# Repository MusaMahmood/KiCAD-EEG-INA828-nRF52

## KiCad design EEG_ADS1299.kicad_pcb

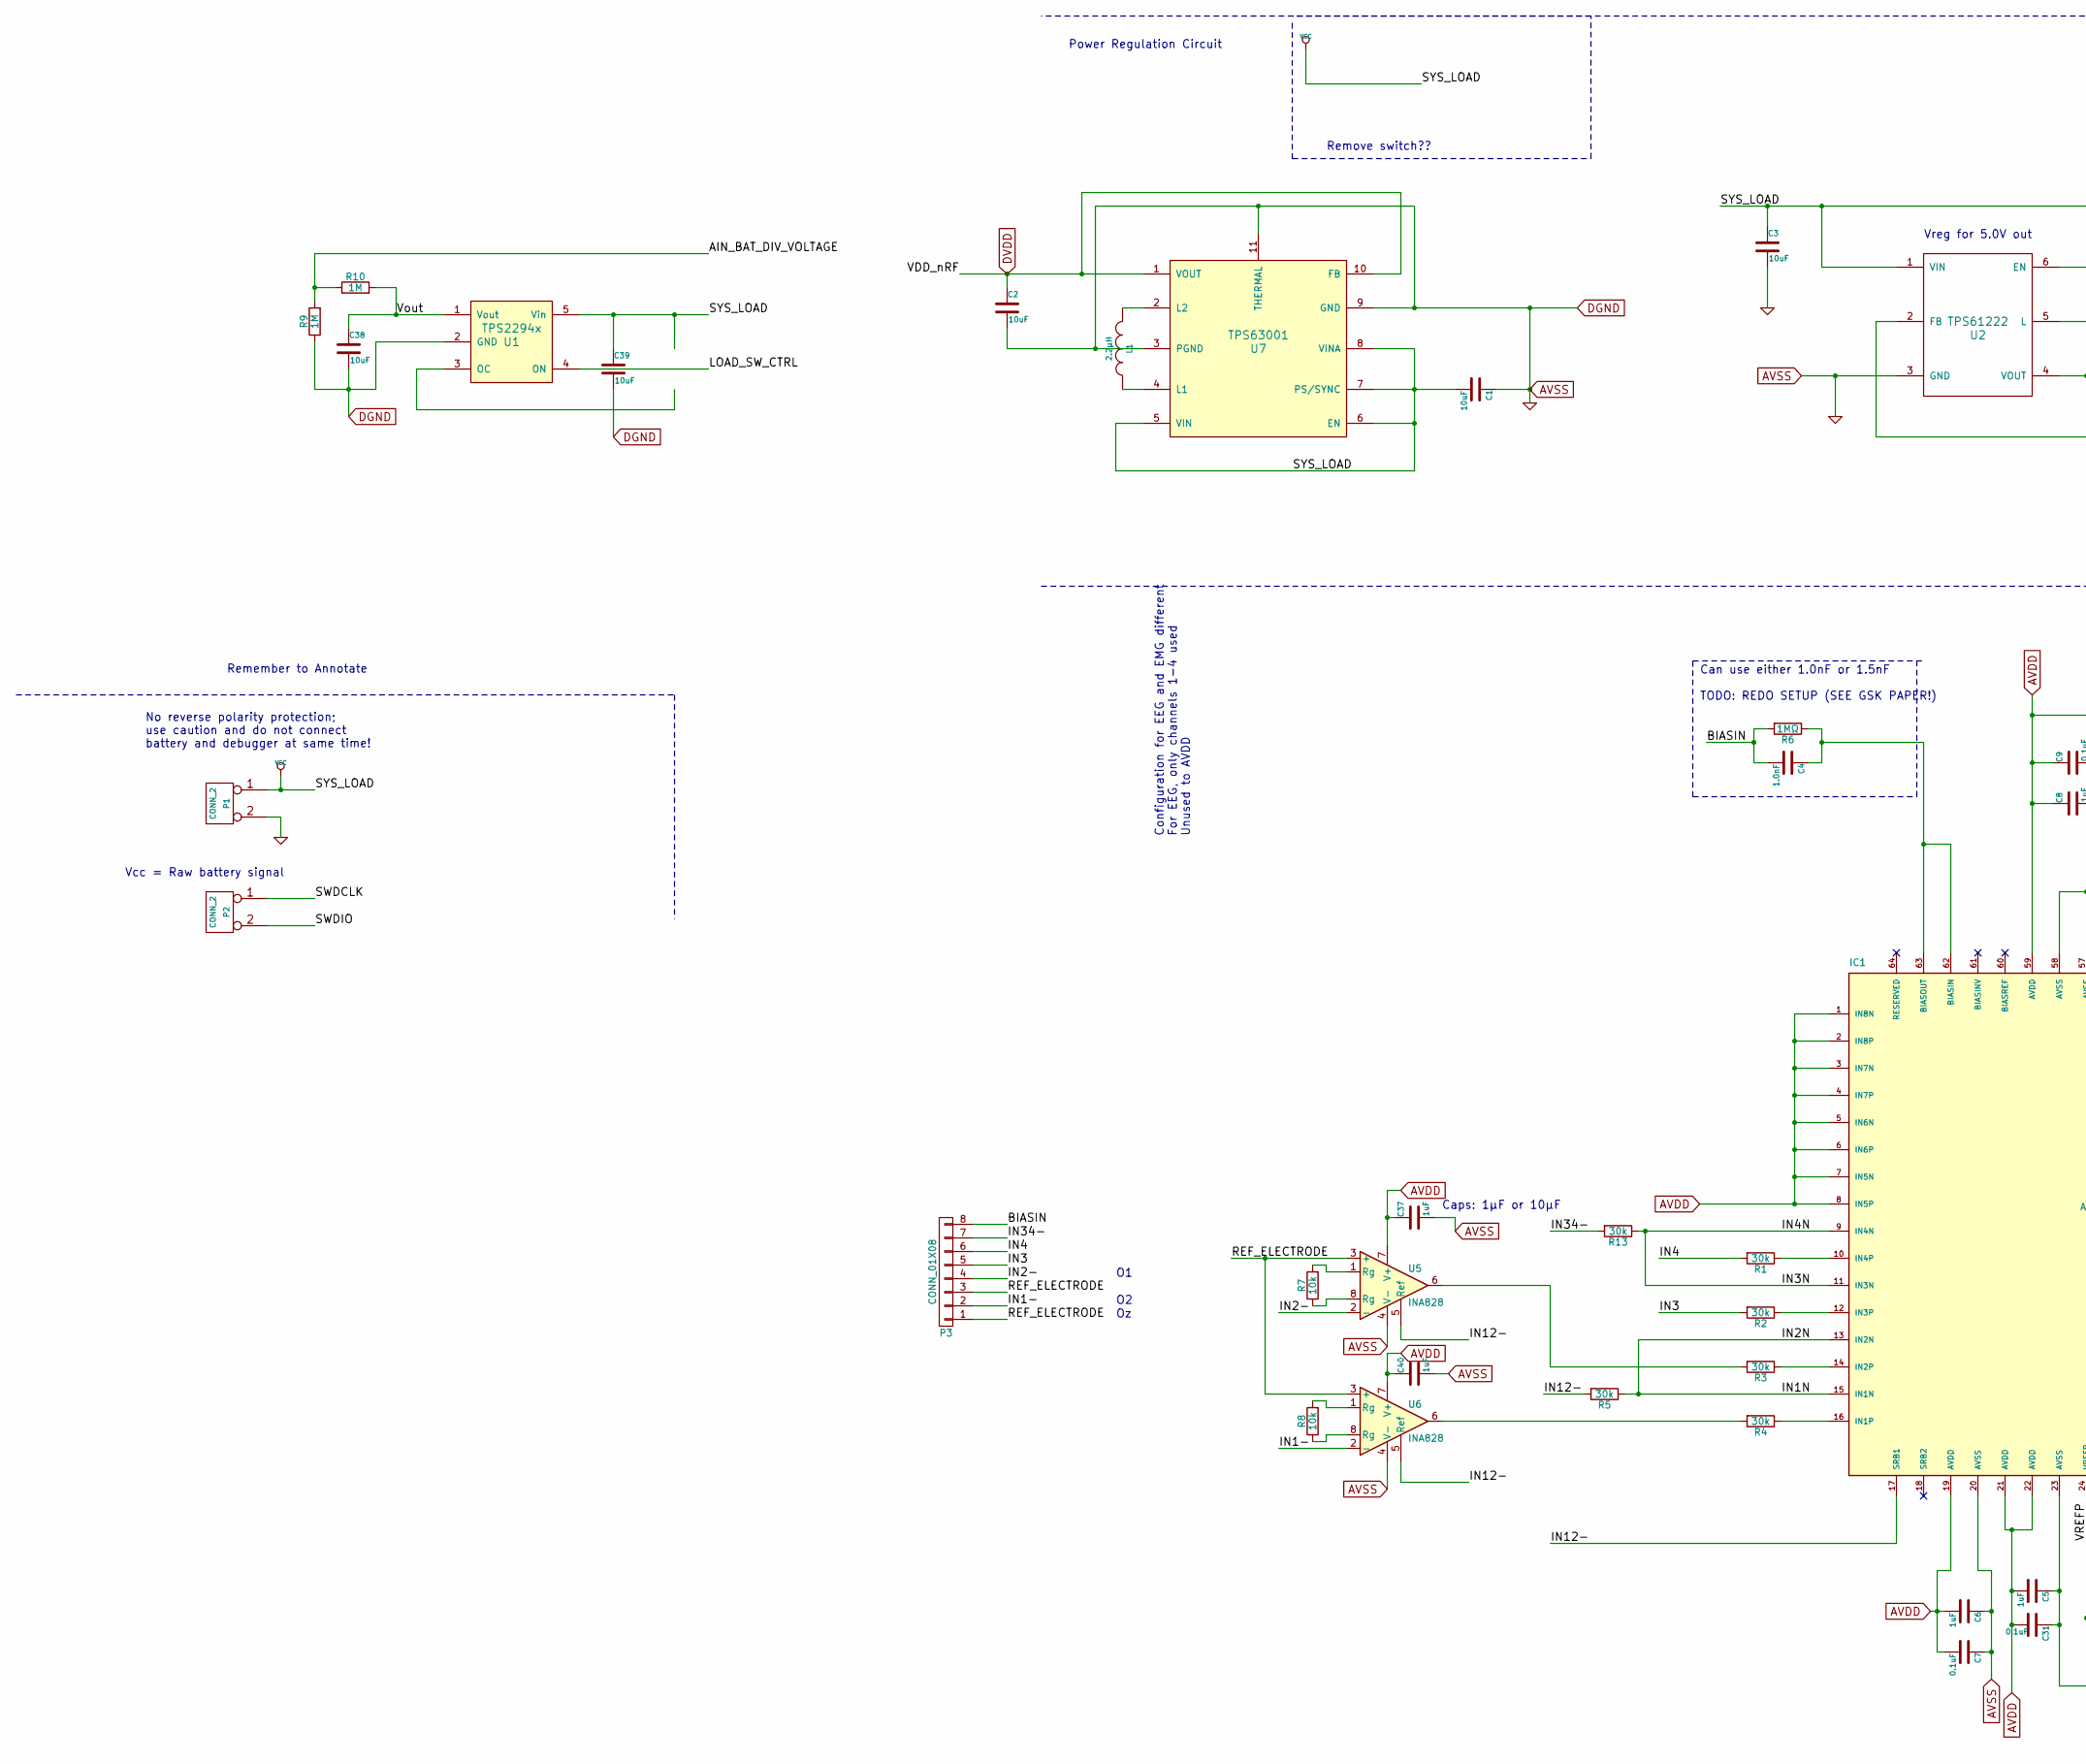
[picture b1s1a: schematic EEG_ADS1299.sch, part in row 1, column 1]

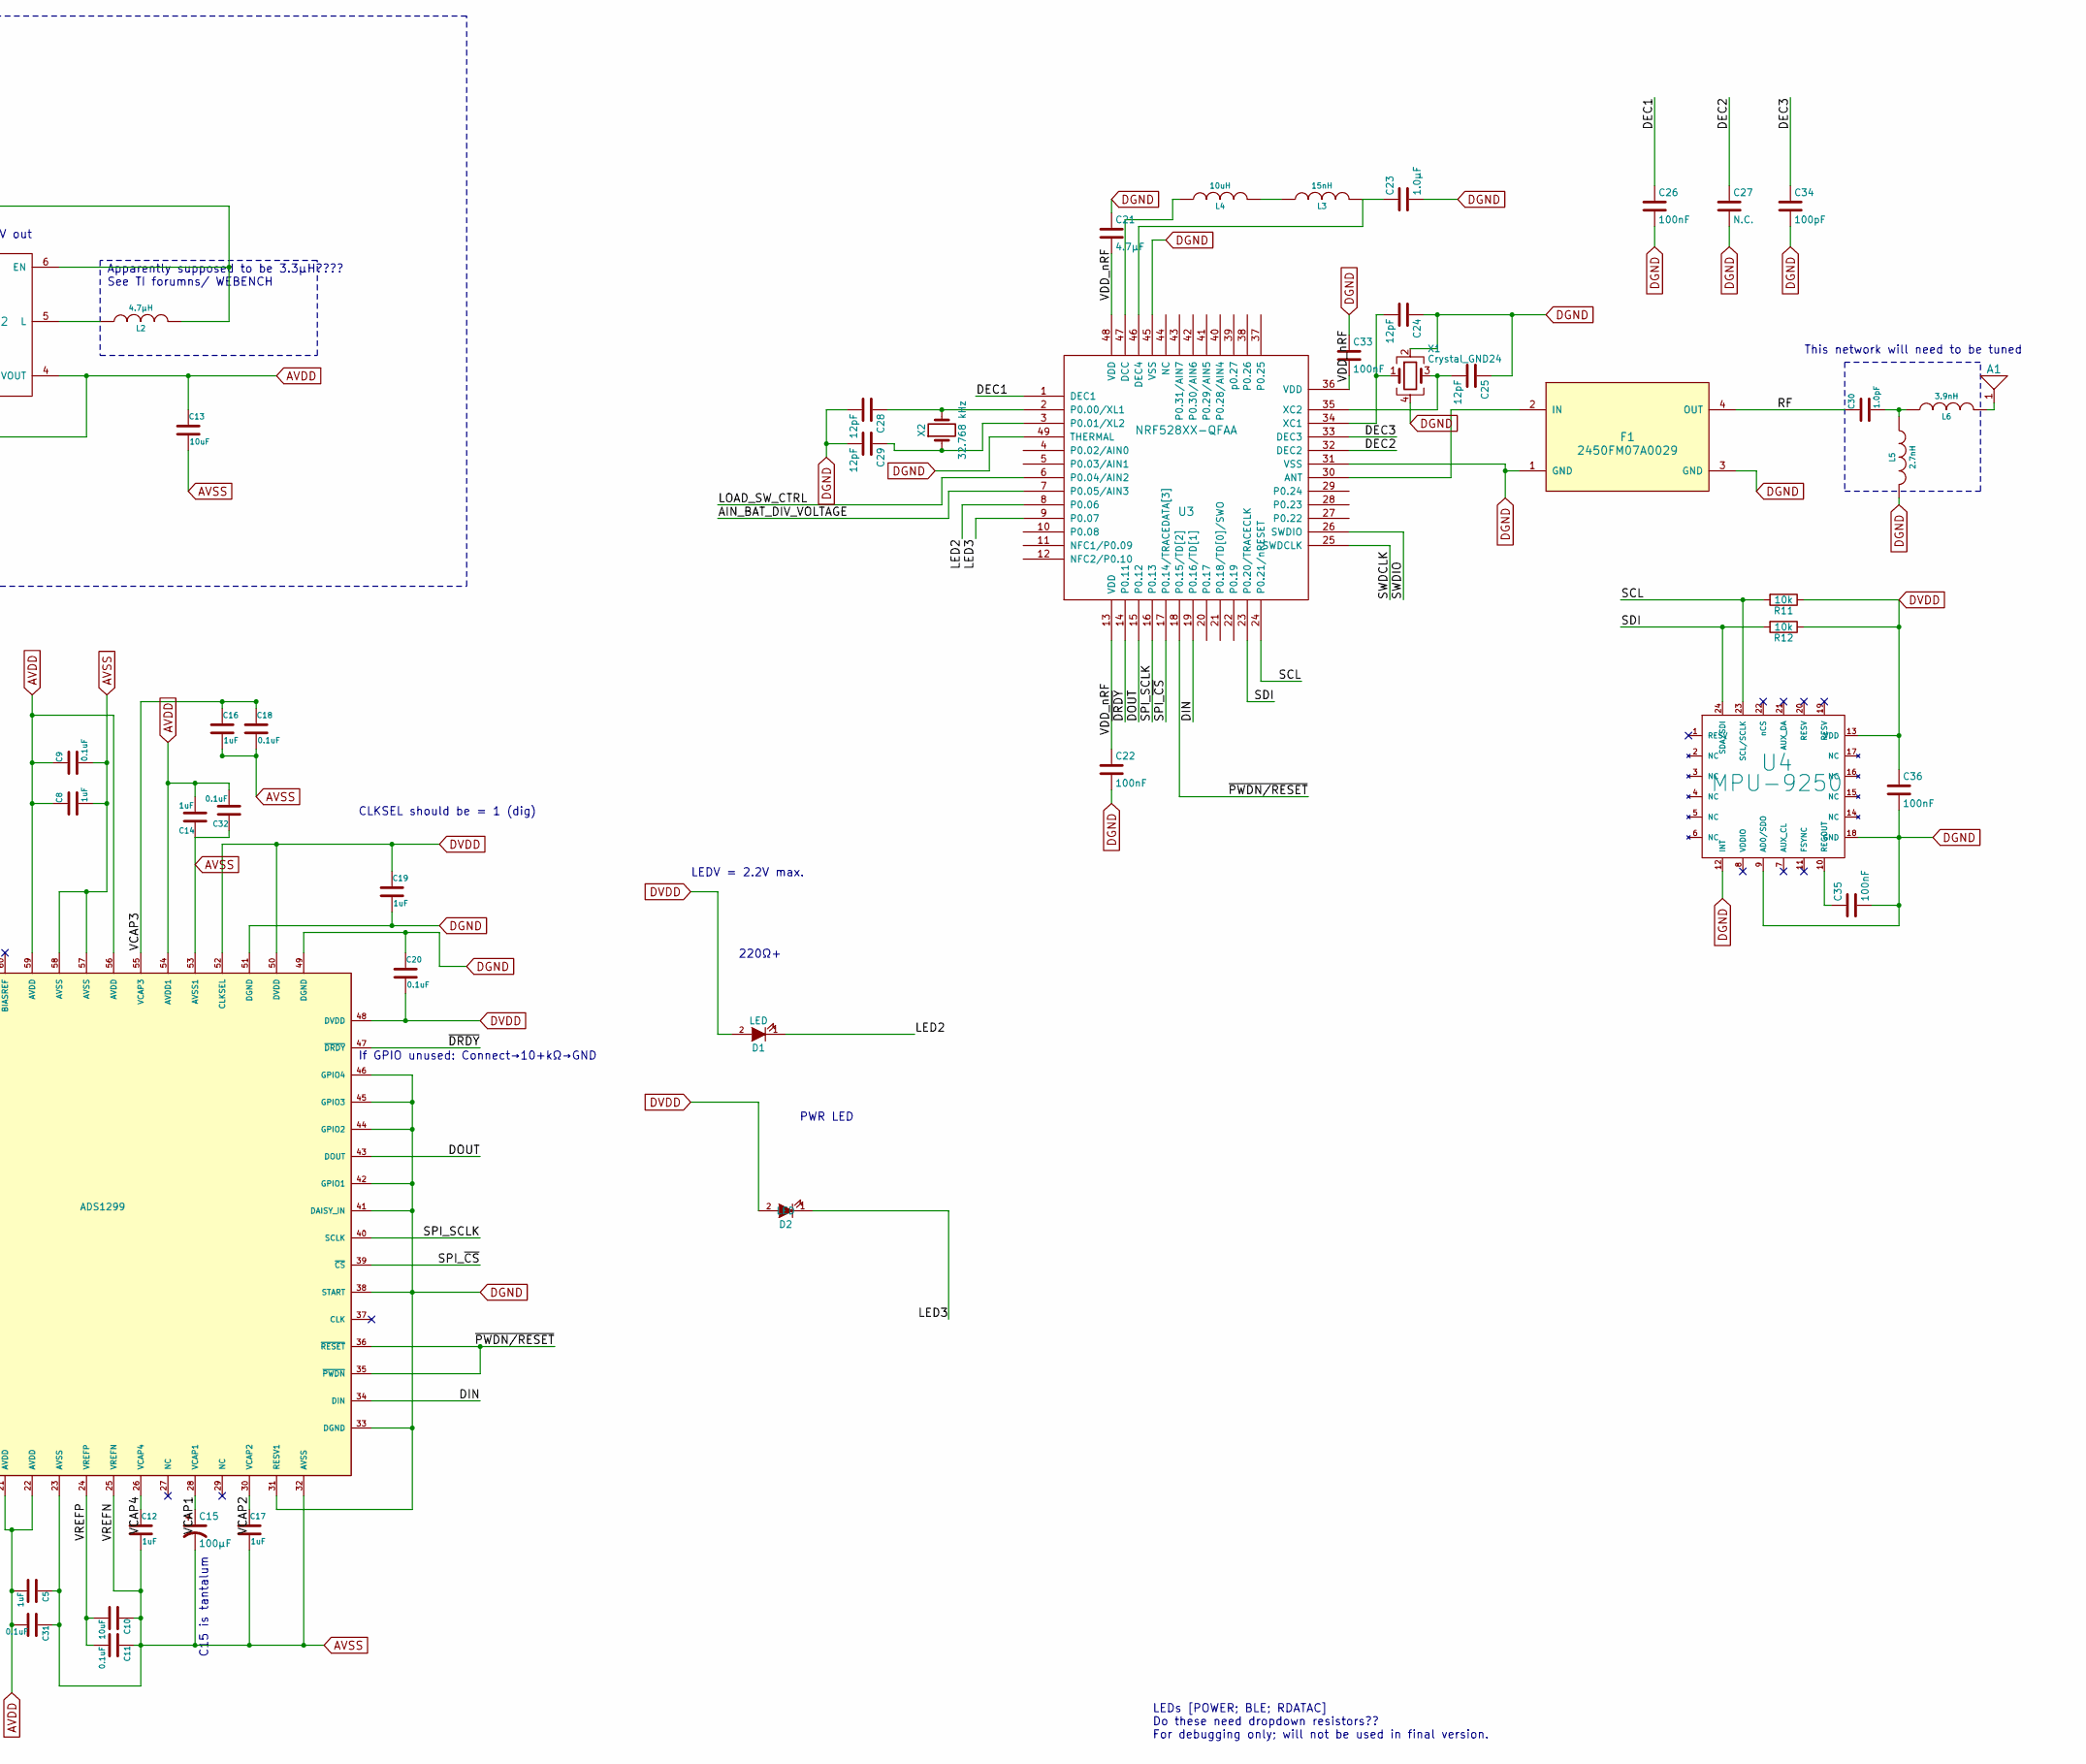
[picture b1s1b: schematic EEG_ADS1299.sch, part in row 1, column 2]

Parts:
A1: CHIP-ANT
C1, C2, C3, C13, C38, C39: 10uF; C_0402
C4: 1.0nF; C_0402
C5, C6, C8, C12, C14, C16, C17, C19, C37, C40: 1uF; C_0402
C7, C9, C11, C18, C20, C31, C32: 0.1uF; C_0402
C10: 10uF; C_0603
C15: 100µF; C_0603
C21: 4.7µF; C_0402
C22: 100nF; C_0603
C23: 1.0µF; C_0603
C24, C25, C28, C29: 12pF; C_0402
C26, C33, C35, C36: 100nF; C_0402
C27: N.C.
C30: 1.0pF; C_0402
C34: 100pF; C_0402
D1, D2: LED; LED_0603
F1: 2450FM07A0029
IC1: ADS1299; TQFP-64_10x10mm_Pitch0.5mm
L1: 2.2µH; L_0603
L2: 4.7µH; L_0603
L3: 15nH; L_0402
L4: 10uH; L_0603
L5: 2.7nH; L_0402
L6: 3.9nH; L_0402
P1, P2: CONN_2; Pin_Header_Straight_1x02_Pitch2.54mm
P3: CONN_01X08
R1, R2, R3, R4, R5, R13: 30k; R_0402
R6: 1MΩ; R_0402
R7, R8, R11, R12: 10k; R_0402
R9, R10: 1M; R_0402
U1: TPS2294x; SOT-353_SC-70-5
U2: TPS61222; SOT-363_SC-70-6
U3: NRF528XX-QFAA; UQFN-48-1EP_6x6mm_Pitch0.4mm
U4: MPU-9250; QFN-24_3x3mm_Pitch0.4mm
U5, U6: INA828; SOIC_8_4.9mm_x_3.91
U7: TPS63001; DFN-10-1EP_3x3mm_Pitch0.5mm
X1: Crystal_GND24; Crystal_SMD_2016-4pin_2.0x1.6mm
X2: 32.768 kHz; Crystal_SMD_2012-2pin_2.0x1.2mm

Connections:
/AIN_BAT_DIV_VOLTAGE: R9.2, R10.1, U3.7 (P0.05/AIN3)
/BIASIN: C4.2, P3.8, R6.2
/DEC1: C26.1, U3.1 (DEC1)
/DEC2: C27.1, U3.32 (DEC2)
/DEC3: C34.1, U3.33 (DEC3)
/DIN: IC1.34 (DIN), U3.19 (P0.16/TD[1])
/DOUT: IC1.43 (DOUT), U3.15 (P0.12)
/IN1-: P3.2, U6.2 (-)
/IN1N: IC1.13 (IN2N), IC1.15 (IN1N), R5.1
/IN2-: P3.4, U5.2 (-)
/IN3: P3.5, R2.2
/IN3N: IC1.9 (IN4N), IC1.11 (IN3N), R13.1
/IN4: P3.6, R1.2
/IN12-: IC1.17 (SRB1), R5.2, U5.5 (Ref), U6.5 (Ref)
/IN34-: P3.7, R13.2
/LED2: D1.1 (K), U3.8 (P0.06)
/LED3: D2.1 (K), U3.9 (P0.07)
/LOAD_SW_CTRL: U1.4 (ON), U3.6 (P0.04/AIN2)
/REF_ELECTRODE: P3.1, P3.3, U5.3 (+), U6.3 (+)
/RF: C30.1, F1.4 (OUT)
/SCL: R11.2, U3.24 (P0.21/nRESET), U4.23 (SCL/SCLK)
/SDI: R12.2, U3.23 (P0.20/TRACECLK), U4.24 (SDA/SDI)
/SPI_SCLK: IC1.40 (SCLK), U3.16 (P0.13)
/SPI_~CS: IC1.39 (~CS), U3.17 (P0.14/TRACEDATA[3])
/SWDCLK: P2.1, U3.25 (SWDCLK)
/SWDIO: P2.2 (PM), U3.26 (SWDIO)
/VCAP1: C15.1, IC1.28 (VCAP1)
/VCAP2: C17.1, IC1.30 (VCAP2)
/VCAP3: C16.1, C18.1, IC1.55 (VCAP3)
/VCAP4: C12.1, IC1.26 (VCAP4)
/VREFP: C10.2, C11.2, IC1.24 (VREFP)
/Vout: C38.1, R10.2, U1.1 (Vout)
/~DRDY: IC1.47 (~DRDY), U3.14 (P0.11)
/~PWDN/RESET: IC1.35 (~PWDN), IC1.36 (~RESET), U3.18 (P0.15/TD[2])
AVDD: C5.2, C6.2, C7.2, C8.1, C9.1, C13.1, C14.2, C31.2, C32.2, C37.1, C40.1, IC1.1 (IN8N), IC1.2 (IN8P), IC1.3 (IN7N), IC1.4 (IN7P), IC1.5 (IN6N), IC1.6 (IN6P), IC1.7 (IN5N), IC1.8 (IN5P), IC1.19 (AVDD), IC1.21 (AVDD), IC1.22 (AVDD), IC1.54 (AVDD1), IC1.56 (AVDD), IC1.59 (AVDD), U2.2 (FB), U2.4 (VOUT), U5.7 (V+), U6.7 (V+)
AVSS: C1.1, C2.2, C3.2, C5.1, C6.1, C7.1, C8.2, C9.2, C10.1, C11.1, C12.2, C13.2, C14.1, C15.2, C16.2, C17.2, C18.2, C19.2, C20.1, C21.1, C22.2, C23.2, C24.1, C25.1, C26.2, C27.2, C28.2, C29.2, C31.1, C32.1, C33.1, C34.2, C35.2, C36.2, C37.2, C38.2, C39.2, C40.2, F1.1 (GND), F1.3 (GND), IC1.20 (AVSS), IC1.23 (AVSS), IC1.25 (VREFN), IC1.31 (RESV1), IC1.32 (AVSS), IC1.33 (DGND), IC1.38 (START), IC1.41 (DAISY_IN), IC1.42 (GPIO1), IC1.44 (GPIO2), IC1.45 (GPIO3), IC1.46 (GPIO4), IC1.49 (DGND), IC1.51 (DGND), IC1.53 (AVSS1), IC1.57 (AVSS), IC1.58 (AVSS), L5.2, P1.2 (PM), R9.1, U1.2 (GND), U2.3 (GND), U3.31 (VSS), U3.45 (VSS), U3.49 (THERMAL), U4.9 (AD0/SDO), U4.12 (INT), U4.18 (GND), U5.4 (V-), U6.4 (V-), U7.3 (PGND), U7.9 (GND), U7.11 (THERMAL), X1.2, X1.4
DVDD: C2.1, C19.1, C20.2, C21.2, C22.1, C33.2, C36.1, D1.2 (A), D2.2 (A), IC1.48 (DVDD), IC1.50 (DVDD), IC1.52 (CLKSEL), R11.1, R12.1, U3.13 (VDD), U3.36 (VDD), U3.48 (VDD), U4.13 (VDD), U7.1 (VOUT), U7.10 (FB)
unnamed: A1.1 (ANT), L6.2
unnamed: C4.1, IC1.62 (BIASIN), IC1.63 (BIASOUT), R6.1
unnamed: C23.1, L3.2, U3.46 (DEC4)
unnamed: C24.2, U3.34 (XC1), X1.1
unnamed: C25.2, U3.35 (XC2), X1.3
unnamed: C28.1, U3.2 (P0.00/XL1), X2.2
unnamed: C29.1, U3.3 (P0.01/XL2), X2.1
unnamed: C30.2, L5.1, L6.1
unnamed: C35.1, U4.10 (REGOUT)
unnamed: F1.2 (IN), U3.30 (ANT)
unnamed: IC1.10 (IN4P), R1.1
unnamed: IC1.12 (IN3P), R2.1
unnamed: IC1.14 (IN2P), R3.1
unnamed: IC1.16 (IN1P), R4.1
unnamed: L1.1, U7.4 (L1)
unnamed: L1.2, U7.2 (L2)
unnamed: L2.1, U2.5 (L)
unnamed: L3.1, L4.2
unnamed: L4.1, U3.47 (DCC)
unnamed: R3.2, U5.6
unnamed: R4.2, U6.6
unnamed: R7.1, U5.8 (Rg)
unnamed: R7.2, U5.1 (Rg)
unnamed: R8.1, U6.8 (Rg)
unnamed: R8.2, U6.1 (Rg)
VCC: C1.2, C3.1, C39.1, L2.2, P1.1, U1.5 (Vin), U2.1 (VIN), U2.6 (EN), U7.5 (VIN), U7.6 (EN), U7.7 (PS/SYNC), U7.8 (VINA)

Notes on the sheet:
This network will need to be tuned
No reverse polarity protection; use caution and do not connect battery and debugger at same time!
Can use either 1.0nF or 1.5nF TODO: REDO SETUP (SEE GSK PAPER!)
Configuration for EEG and EMG different For EEG, only channels 1-4 used Unused to AVDD
Remember to Annotate
If GPIO unused: Connect→10+kΩ→GND
Vreg for 5.0V out
LEDs [POWER; BLE; RDATAC] Do these need dropdown resistors?? For debugging only; will not be used in final version.
Power Regulation Circuit
Vcc = Raw battery signal
CLKSEL should be = 1 (dig)
C15 is tantalum
Apparently supposed to be 3.3µH???? See TI forumns/ WEBENCH
Remove switch??
220Ω+
LEDV = 2.2V max.
PWR LED
Caps: 1µF or 10µF

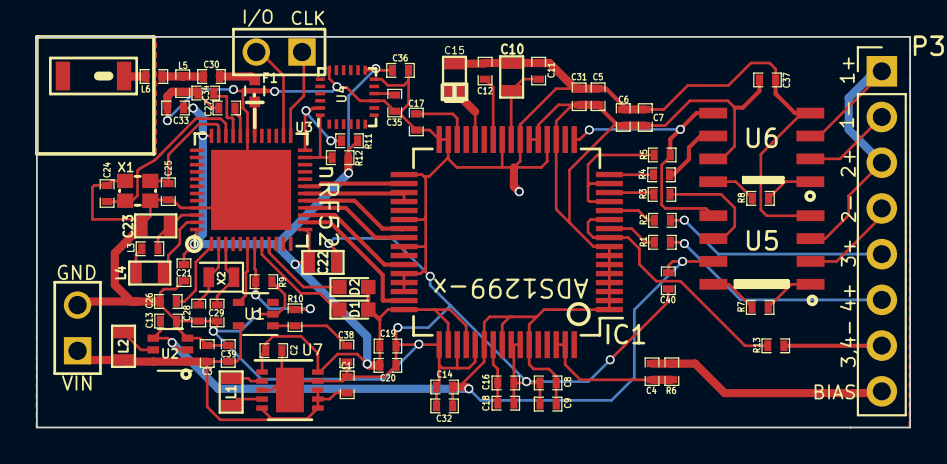
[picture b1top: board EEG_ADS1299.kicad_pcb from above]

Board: 2 copper layers, 48.5 x 21.7 mm, 76 parts (0 on the bottom side), 63 nets.

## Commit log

2017-12-04 Reorganized libraries into 'libs/' folder, footprint associations, fixed schematic.
2017-12-04 Updated schematic, deleted extra pin headers. Removed extra components from pcb file.
2017-12-04 Finished pcb draft for 4-ch with 2x INA828 (single-ended only).
2017-12-04 Updated gerber files.
2017-12-06 (#1) - Added single capacitor on amp inputs. (C37)
2017-12-12 Added TPS63001, TPS22941.
2017-12-12 Fixed design and separated channels 1 and 2 from 3 and 4, with 1 and 2 being the pre-amplified circuits.
2017-12-13 Updated front mask for correct information + gerber files for v3.2
2017-12-13 Fixed #5, and fixed back silkscreen.
2018-01-08 Update Schematic for ADS1299/INA828 Removing INA828 from circuit. Shorting negative inputs in pairs.
2018-01-09 Revert to old design.
2018-03-07 Updated schematic and pcb design to reflect final EEG design: Connected SRB1 to IN12-.
